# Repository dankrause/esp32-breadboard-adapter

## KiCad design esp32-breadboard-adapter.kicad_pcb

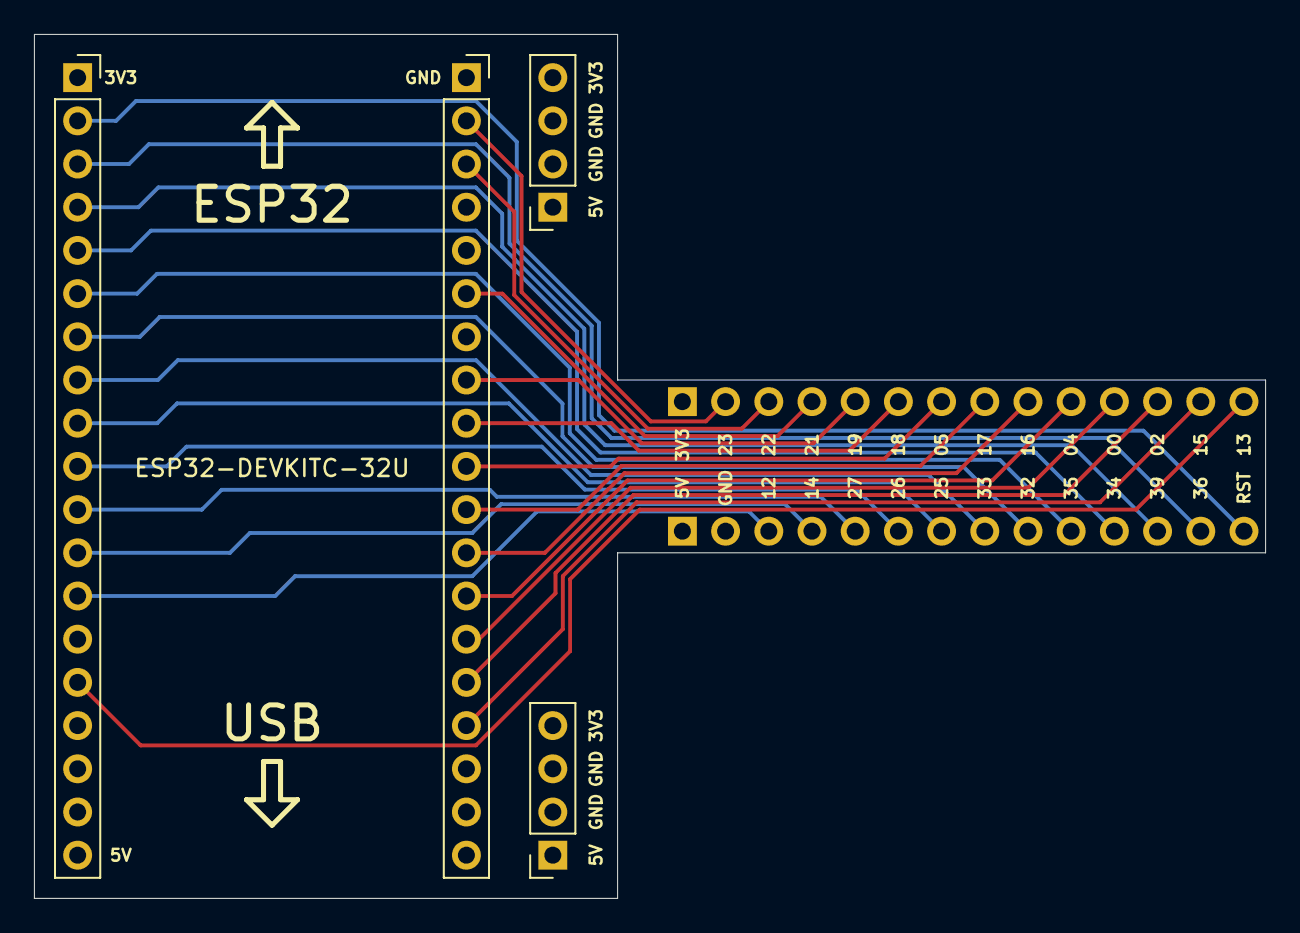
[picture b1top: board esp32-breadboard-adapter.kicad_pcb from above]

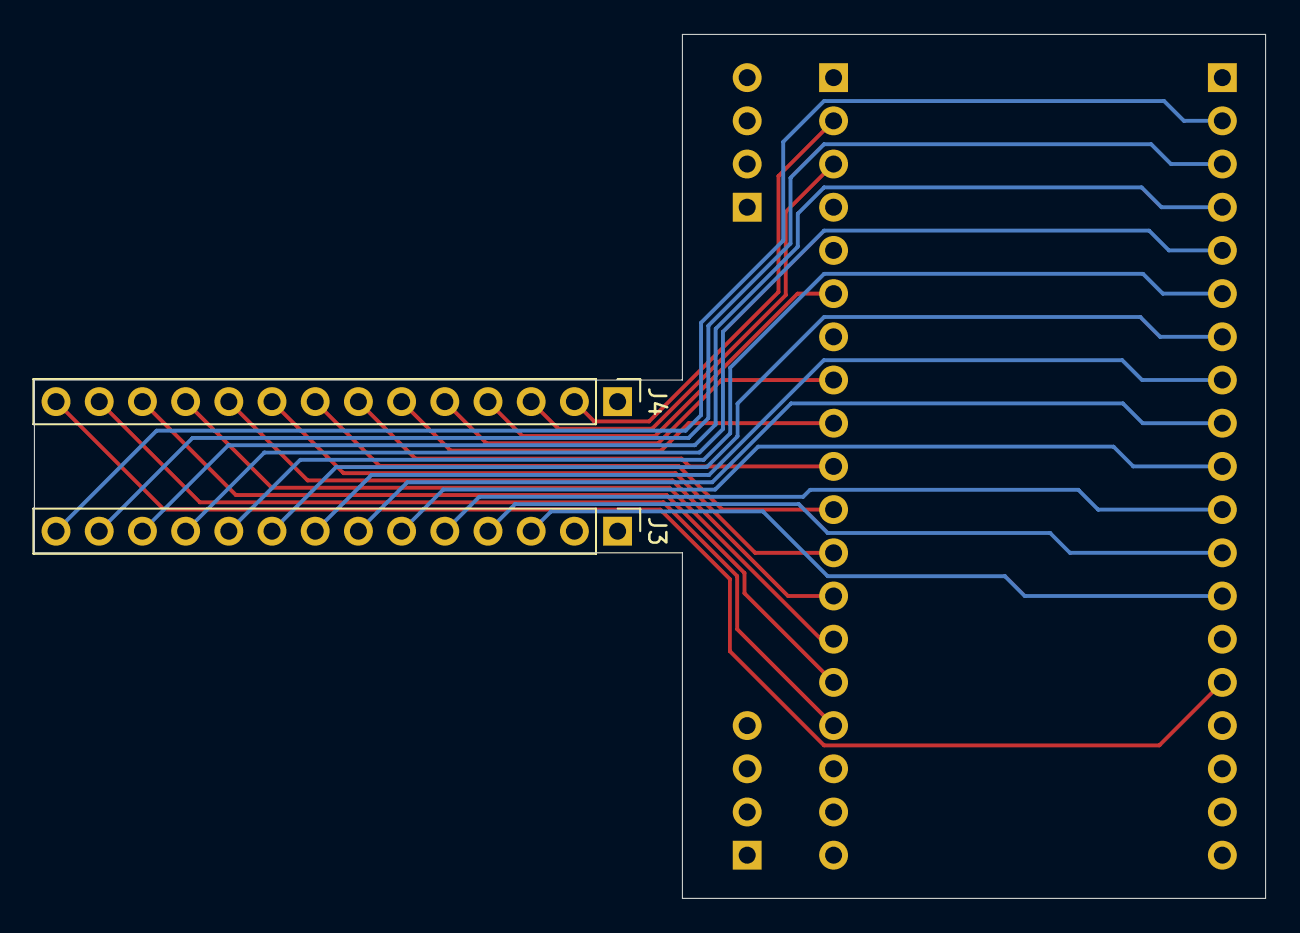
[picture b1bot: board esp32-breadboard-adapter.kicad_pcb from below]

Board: 4 copper layers, 72.4 x 50.8 mm, 6 parts (2 on the bottom side), 28 nets.

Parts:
J1, J2: Conn_01x19_Female; PinSocket_1x19_P2.54mm_Vertical
J3, J4: Conn_01x14_Female; PinHeader_1x14_P2.54mm_Vertical
J5, J6: Conn_01x04_Female; PinSocket_1x04_P2.54mm_Vertical

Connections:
+3V3: J1.1, J4.1, J5.4, J6.4
+5V: J1.19, J3.1, J5.1, J6.1
GND: J1.14, J2.1, J2.7, J3.2, J5.2, J5.3, J6.2, J6.3
GPIO00: J2.14, J4.11
GPIO02: J2.15, J4.12
GPIO04: J2.13, J4.10
GPIO05: J2.10, J4.7
GPIO12: J1.13, J3.3
GPIO13: J1.15, J4.14
GPIO14: J1.12, J3.4
GPIO15: J2.16, J4.13
GPIO16: J2.12, J4.9
GPIO17: J2.11, J4.8
GPIO18: J2.9, J4.6
GPIO19: J2.8, J4.5
GPIO21: J2.6, J4.4
GPIO22: J2.3, J4.3
GPIO23: J2.2, J4.2
GPIO25: J1.9, J3.7
GPIO26: J1.10, J3.6
GPIO27: J1.11, J3.5
GPIO32: J1.7, J3.9
GPIO33: J1.8, J3.8
GPIO34: J1.5, J3.11
GPIO35: J1.6, J3.10
GPIO36: J1.3, J3.13
GPIO39: J1.4, J3.12
RESET: J1.2, J3.14
